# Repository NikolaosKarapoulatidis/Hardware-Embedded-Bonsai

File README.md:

# Hardware Engineering and Advanced Embedded Lab

Team Bonsai

Github Repository belongs to the following members:
1) Shehroz Bashir Malik
2) Christian Stratmann
3) Nikolaos Karapoulatidis

We are students in Hochschule Hamm-Lippstadt studying in our 6th Semester. This course is supervised by Professor Ali Hayek. The repository will contain our lab work which consists of:

1) Coding Exercises in VHDL
2) VGA Driver Implemented in VHDL
3) Arduino IOT Project connected to a Raspberry Pi using MQTT

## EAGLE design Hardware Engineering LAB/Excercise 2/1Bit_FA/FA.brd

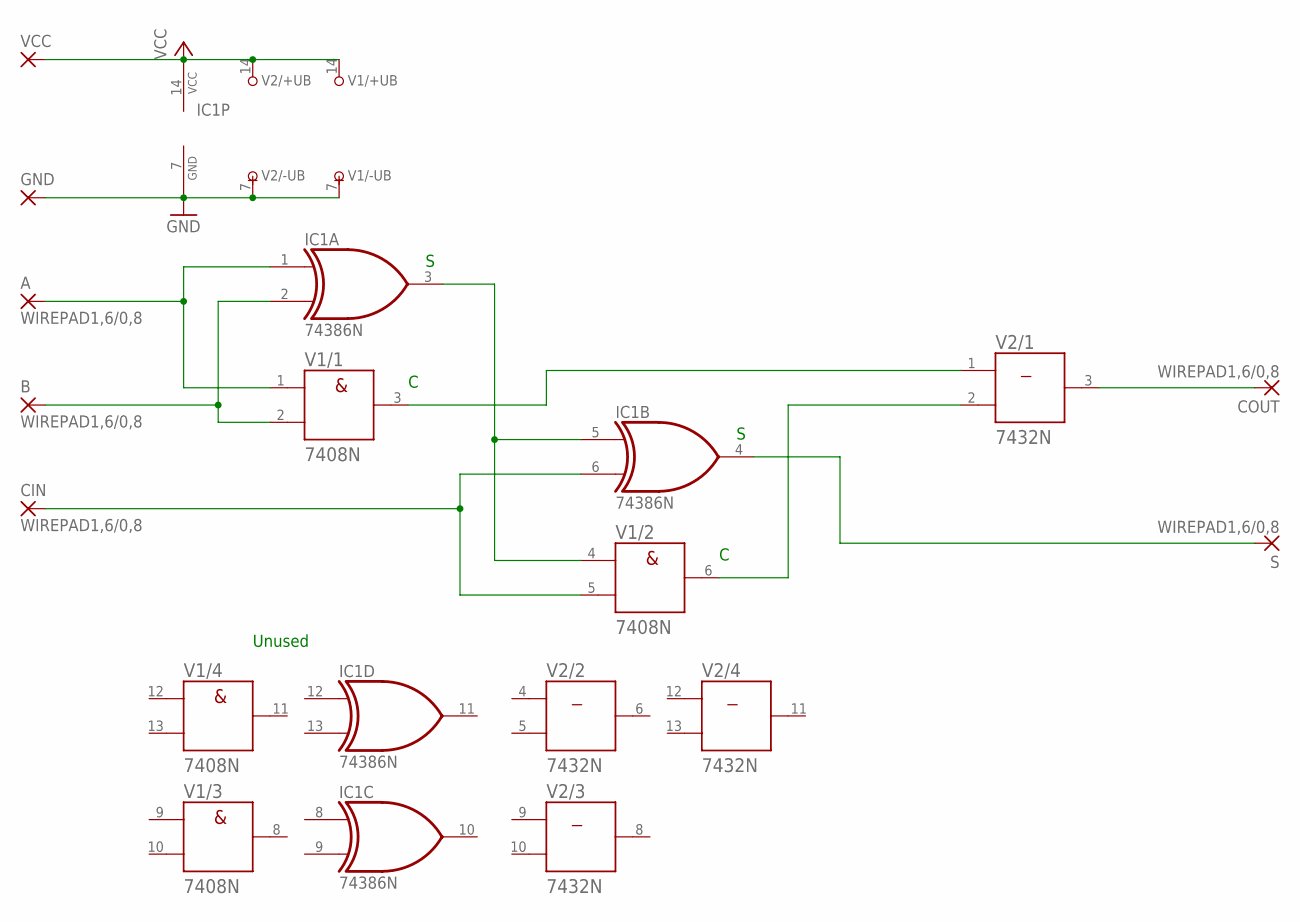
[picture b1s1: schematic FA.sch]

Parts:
A: WIREPAD1,6/0,8; 1,6/0,8
B: WIREPAD1,6/0,8; 1,6/0,8
CIN: WIREPAD1,6/0,8; 1,6/0,8
COUT: WIREPAD1,6/0,8; 1,6/0,8
GND: 1,6/0,8
IC1: 74386N; DIL14
S: WIREPAD1,6/0,8; 1,6/0,8
V1: 7408N; DIL14
V2: 7432N; DIL14
VCC: 1,6/0,8

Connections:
GND: GND.1, IC1.7 (GND), V1.7 (-UB), V2.7 (-UB)
unnamed: A.1, IC1.1 (I0), V1.1 (A)
unnamed: B.1, IC1.2 (I1), V1.2 (B)
unnamed: IC1.3 (O), IC1.5 (I0), V1.4 (A)
unnamed: CIN.1, IC1.6 (I1), V1.5 (B)
unnamed: V1.3 (Y), V2.1 (A)
unnamed: IC1.4 (O), S.1
unnamed: V1.6 (Y), V2.2 (B)
unnamed: COUT.1, V2.3 (Y)
VCC: IC1.14 (VCC), V1.14 (+UB), V2.14 (+UB), VCC.1

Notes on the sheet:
Unused

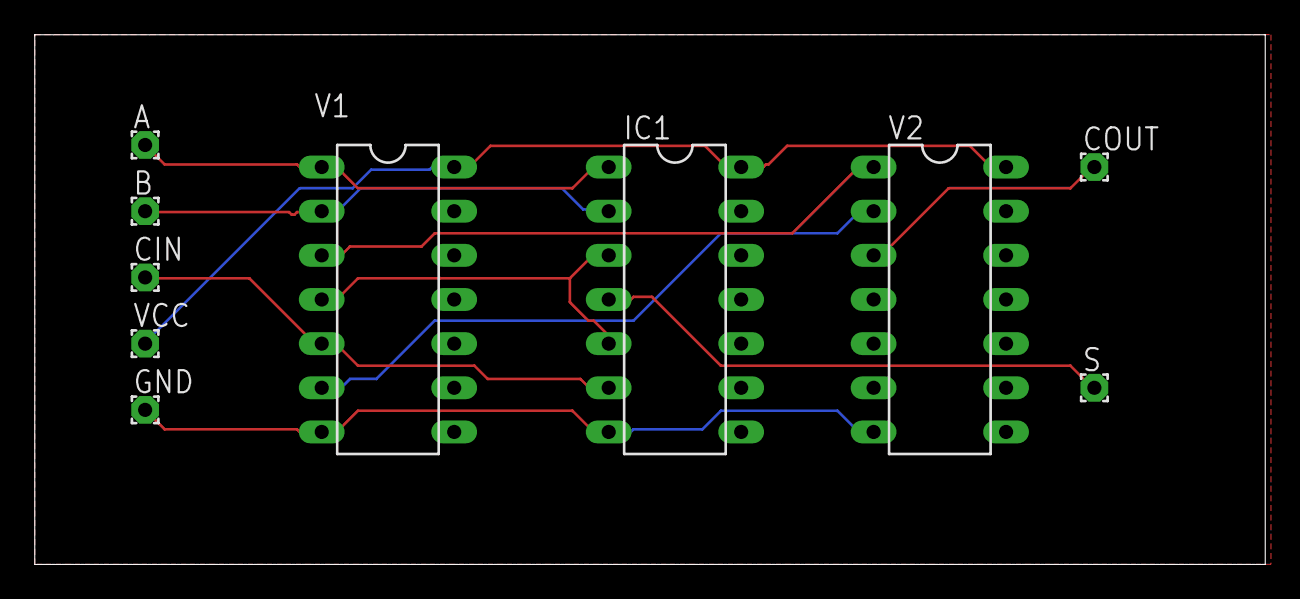
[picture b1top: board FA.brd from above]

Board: 2 copper layers, 70.8 x 30.5 mm, 10 parts (0 on the bottom side), 10 nets.

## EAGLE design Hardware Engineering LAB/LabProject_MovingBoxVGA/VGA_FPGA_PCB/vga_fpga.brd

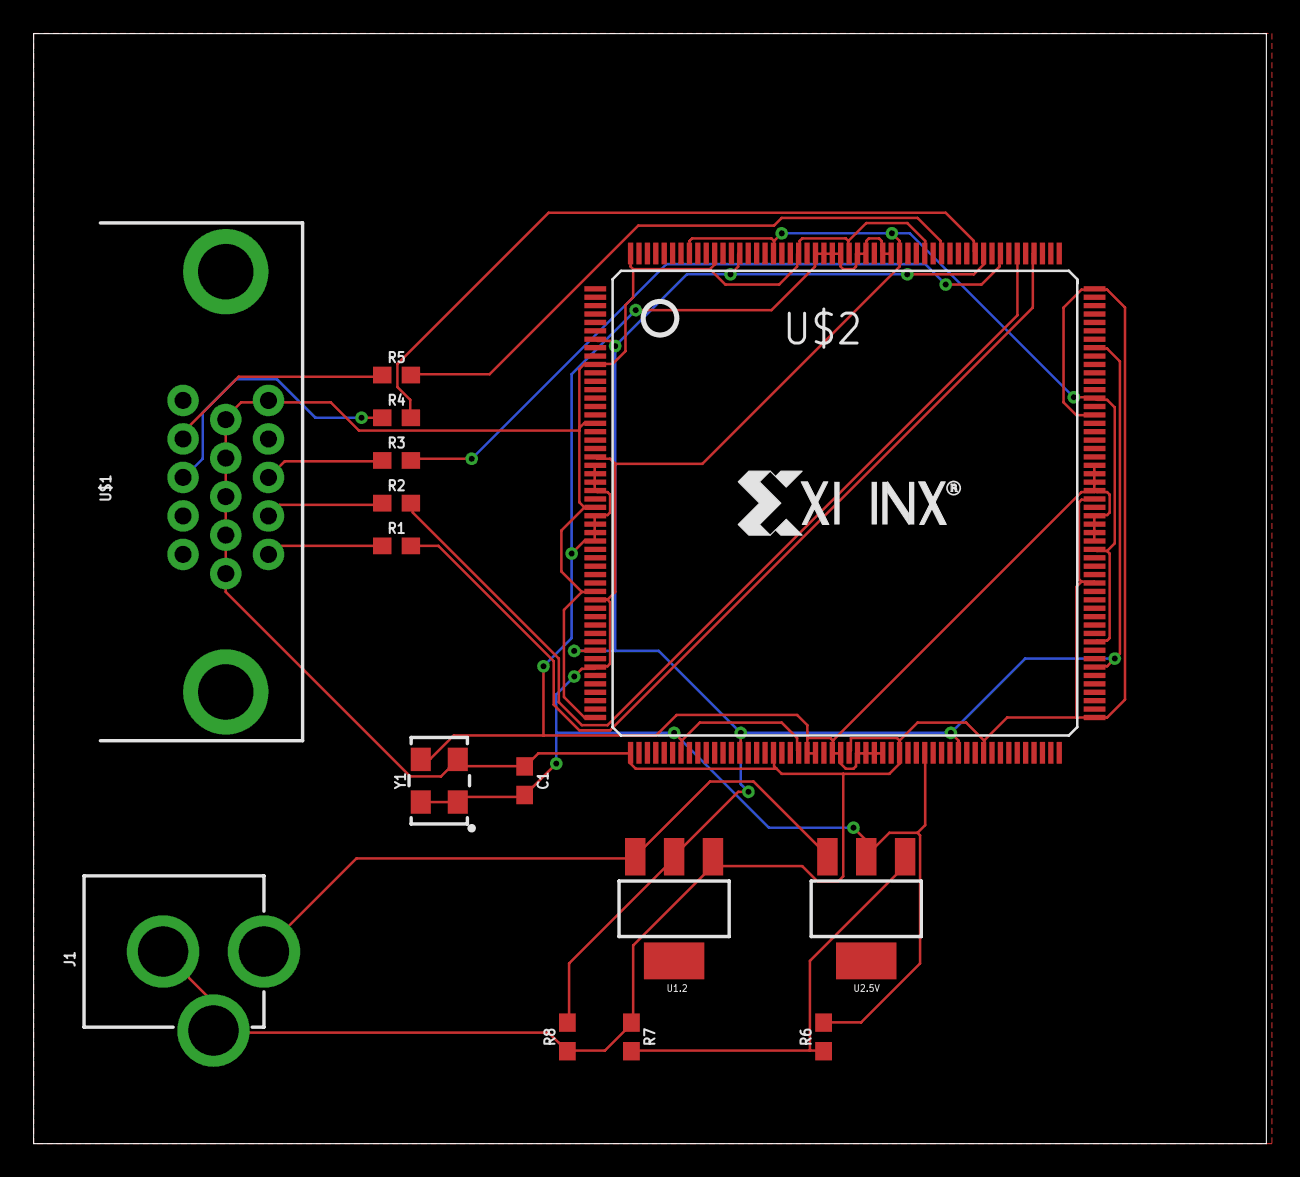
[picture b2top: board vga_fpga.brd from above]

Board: 2 copper layers, 73.3 x 66.0 mm, 15 parts (0 on the bottom side), 16 nets.

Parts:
C1: 0.1uF; 0603
J1: POWER_JACK; POWER_JACK_PTH
R1, R2, R3: 270; 0603
R4, R5: 82.5; 0603
R6, R7, R8: 1000; 0603
U1.2, U2.5V: V_REG_317SMD; SOT223
U$1: DB15
U$2: XC3S250/500E-PQ208; PQ208
Y1: OSCILLATORSMD-5X3; OSCILLATOR-SMD-5X3.2

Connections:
GND: C1.1, J1.GND, J1.GNDBREAK, R7.1, R8.1, U1.2.1, U$1.5, U$1.6, U$1.7, U$1.8, U$1.9, U$1.10, U$2.10, U$2.17, U$2.27, U$2.37, U$2.52, U$2.53, U$2.70, U$2.79, U$2.85, U$2.95, U$2.105, U$2.121, U$2.131, U$2.141, U$2.156, U$2.173, U$2.182, U$2.188, U$2.198, U$2.208, Y1.2
unnamed: J1.PWR, U1.2.3, U2.5V.3
unnamed: R8.2, U1.2.2, U$2.7, U$2.44, U$2.66, U$2.92, U$2.111, U$2.149, U$2.166, U$2.195
unnamed: R1.1, U$1.1
unnamed: R2.1, U$1.2
unnamed: R6.1, R7.2, U2.5V.1
unnamed: C1.2, R6.2, U2.5V.2, U$2.21, U$2.38, U$2.46, U$2.59, U$2.73, U$2.88, U$2.114, U$2.125, U$2.143, U$2.176, U$2.191, U$2.201, Y1.1, Y1.4
unnamed: R3.1, U$1.3
unnamed: R4.1, U$1.13
unnamed: R5.1, U$1.14
unnamed: R1.2, U$2.160
unnamed: R2.2, U$2.162
unnamed: R3.2, U$2.164
unnamed: R4.2, U$2.167
unnamed: R5.2, U$2.171
unnamed: U$2.22, U$2.23, U$2.24, U$2.25, U$2.28, U$2.29, U$2.30, U$2.31, U$2.74, U$2.75, U$2.77, U$2.78, U$2.80, U$2.81, U$2.82, U$2.83, U$2.126, U$2.127, U$2.128, U$2.129, U$2.132, U$2.133, U$2.134, U$2.135, U$2.177, U$2.178, U$2.180, U$2.181, U$2.183, U$2.184, U$2.185, U$2.186, Y1.3

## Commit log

2022-05-09 Folder creation plus test file
2022-05-09 Readme
2022-05-09 lab upload \(^.^)/
2022-05-09 upload :D
2022-05-12 D Flip-Flip XDD
2022-05-12 8 bit register
2022-05-12 counting shit
2022-05-13 Docu
2022-06-02 Task 2 -> done
    \(^.^)/
2022-06-07 task 4
2022-06-09 Create Initial_VGA_Code
2022-06-22 bugfixes and implementation
2022-06-22 implementation updates
2022-06-23 Xilinx Implementation Completed
2022-06-23 Video Implementation Plant Nurse
2022-06-23 FPGA completed
2022-06-23 Presentation uploaded
2022-06-23 final documentation
2022-06-24 update VGA pcb
2022-06-24 diagrams uploaded
2022-06-24 Create bom
2022-06-24 Final documentation completed
2022-07-06 xilinx report files automatically generated
2022-07-06 Final Presentation Uploaded

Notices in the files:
parts and their libraries:
SparkFun-Capacitors: Licensing: Creative Commons ShareAlike 4.0 International - https://creativecommons.org/licenses/by-sa/4.0
